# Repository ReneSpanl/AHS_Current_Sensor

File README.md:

This is a isolation amplifier connected with a Shunt in order to measure currents. In the normal BOM it is calculated to fullfill the HCPL-7800 with around 100mA of Current.

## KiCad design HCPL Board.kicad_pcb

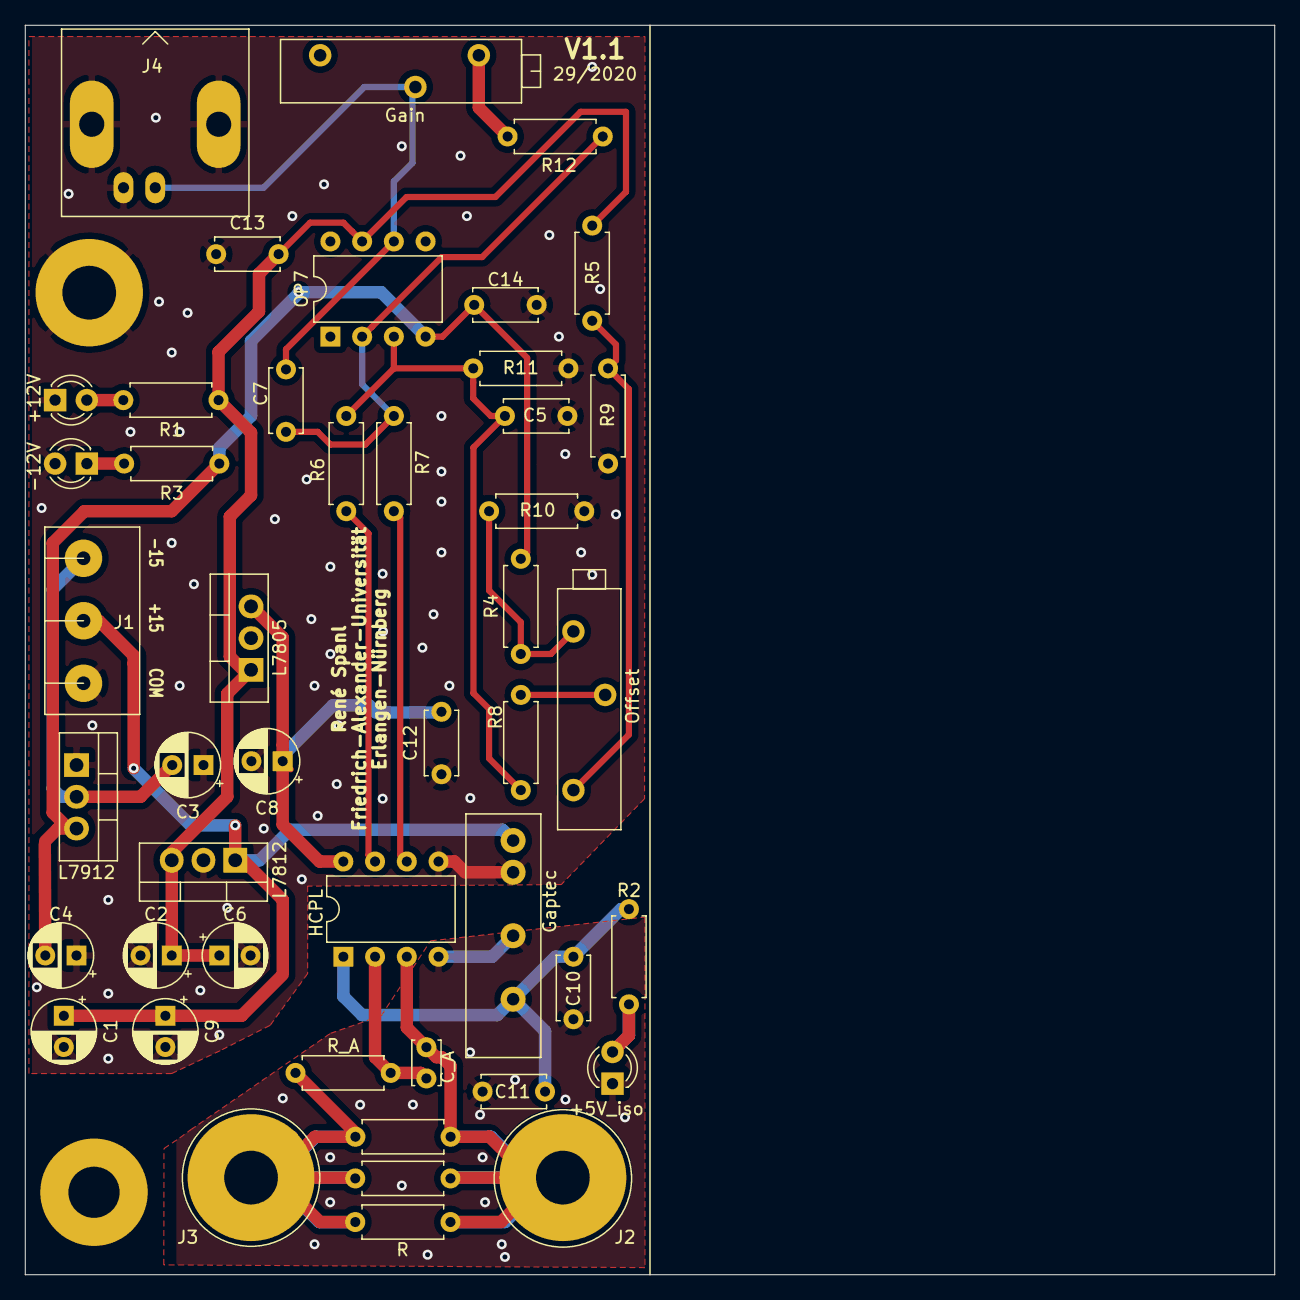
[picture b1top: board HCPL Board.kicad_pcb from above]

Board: 2 copper layers, 100.0 x 100.0 mm, 46 parts (0 on the bottom side), 23 nets.

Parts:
+5V_iso, +12V: LED; LED_D3.0mm
-12V: LED; LED_D3.0mm
C1, C6: 0.33uF; CP_Radial_D5.0mm_P2.50mm
C2, C8: 0.1uF; CP_Radial_D5.0mm_P2.50mm
C3: 10uF; CP_Radial_D5.0mm_P2.50mm
C4: 1uF; CP_Radial_D5.0mm_P2.50mm
C5, C7: 22n; C_Disc_D5.0mm_W2.5mm_P5.00mm
C9: 2.2uF; CP_Radial_D5.0mm_P2.50mm
C10: 0.47uF; C_Disc_D5.0mm_W2.5mm_P5.00mm
C11, C12, C13, C14: 100n; C_Disc_D5.0mm_W2.5mm_P5.00mm
C_A: 0.01u; C_Disc_D3.4mm_W2.1mm_P2.50mm
Gain: 20k; Potentiometer_Bourns_3006P_Horizontal
Gaptec: 1S7E_1.5UP-HCPL_Board; Gaptec_1S7E_1505S1.5UP
HCPL: HCPL-7800; DIP-8_W7.62mm
J1: Conn_01x03_Female; Conn_01x03_Female_Scre
J2, J3: Conn_01x01_Female; Banana_Jack_1Pin
J4: Conn_Coaxial; BNC_Amphenol_B6252HB-NPP3G-50_Horizontal
L7805: L7805; TO-220-3_Vertical
L7812: L7812; TO-220-3_Vertical
L7912: L7912; TO-220-3_Vertical
OP7: OP07; DIP-8_W7.62mm
Offset: 5k; Potentiometer_Bourns_3006P_Horizontal
R: 1; R_Axial_DIN0207_L6.3mm_D2.5mm_P7.62mm_Horizontal
R1, R3: 3.9k; R_Axial_DIN0207_L6.3mm_D2.5mm_P7.62mm_Horizontal
R2: 1.2k; R_Axial_DIN0207_L6.3mm_D2.5mm_P7.62mm_Horizontal
R4, R5, R9, R10: 4,7k; R_Axial_DIN0207_L6.3mm_D2.5mm_P7.62mm_Horizontal
R6, R7, R12: 2.2k; R_Axial_DIN0207_L6.3mm_D2.5mm_P7.62mm_Horizontal
R8, R11: 10k; R_Axial_DIN0207_L6.3mm_D2.5mm_P7.62mm_Horizontal
R_A: 47; R_Axial_DIN0207_L6.3mm_D2.5mm_P7.62mm_Horizontal
R_Shunt1, R_Shunt2: 1; R_Axial_DIN0207_L6.3mm_D2.5mm_P7.62mm_Horizontal

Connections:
5V_iso: C10.1, C11.2, Gaptec.6, HCPL.1, R2.1
+5V: C8.1, C12.2, HCPL.8, L7805.3
+12V: C2.1, C6.1, C13.2, L7805.1, L7812.3, OP7.7, R1.1, R5.2
+15V: C1.1, C9.1, Gaptec.1, J1.2, L7812.1
-12V: C4.2, C14.2, L7912.3, OP7.4, R3.1, R4.2
-15V: C3.2, J1.1, L7912.2
GND: +12V.1, -12V.2, C1.2, C2.2, C3.1, C4.1, C5.2, C6.2, C8.2, C9.2, C12.1, C13.1, C14.1, Gaptec.2, HCPL.5, J1.3, J4.2, L7805.2, L7812.2, L7912.1, R9.1, R10.1, R11.2
GND2: +5V_iso.1, C10.2, C11.1, Gaptec.4, HCPL.4
unnamed: +5V_iso.2, R2.2
unnamed: +12V.2, R1.2
unnamed: -12V.1, R3.2
unnamed: C5.1, OP7.3, R6.1, R8.1, R11.1
unnamed: C7.1, OP7.2, R7.1, R12.2
unnamed: C7.2, Gain.2, J4.1, OP7.6
unnamed: C_A.1, HCPL.2, R_A.1
unnamed: Gain.3, R12.1
unnamed: HCPL.6, R7.2
unnamed: HCPL.7, R6.2
unnamed: Offset.1, R5.1, R9.2
unnamed: Offset.2, R8.2
unnamed: Offset.3, R4.1, R10.2
SIGNAL_IN: J3.1, R.1, R_A.2, R_Shunt1.1, R_Shunt2.1
SIGNAL_OUT: C_A.2, HCPL.3, J2.1, R.2, R_Shunt1.2, R_Shunt2.2

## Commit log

2021-05-28 Last Change
